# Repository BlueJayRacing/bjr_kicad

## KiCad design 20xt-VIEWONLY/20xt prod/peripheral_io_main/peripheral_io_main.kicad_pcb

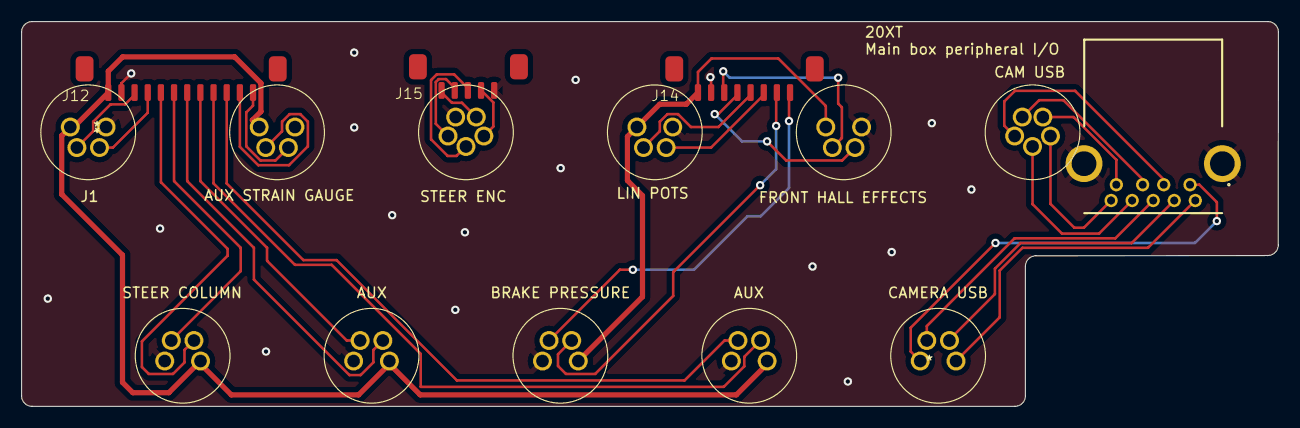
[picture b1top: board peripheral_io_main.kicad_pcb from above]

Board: 2 copper layers, 119.4 x 36.6 mm, 15 parts (0 on the bottom side), 32 nets.

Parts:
J1, J2, J3, J4, J5, J6, J7, J8, J9: Conn_01x04; CONN_T4041017041-000_TEC
J10, J11: Conn_01x05; 5pth
J12: Conn_01x12; SMD_picoblade_hori_1x12
J14: Conn_01x08; SMD_picoblade_hori_1x08
J15: Conn_01x05; SMD_picoblade_hori_1x05
J19: Conn_01x11; 1932258-1

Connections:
GND: J1.3, J2.3, J3.3, J4.3, J5.3, J6.3, J7.3, J9.3, J10.4, J12.11, J14.7, J15.1, J19.10, J19.11
unnamed: J1.2, J12.10
unnamed: J1.4, J12.9
unnamed: J10.1, J15.2
unnamed: J10.2, J15.5
unnamed: J10.3, J15.4
unnamed: J10.5, J15.3
unnamed: J11.1, J19.5
unnamed: J11.2, J19.4
unnamed: J11.3, J19.2
unnamed: J11.4, J19.3
unnamed: J11.5, J19.6
unnamed: J5.4, J12.1
unnamed: J5.2, J12.2
unnamed: J4.4, J12.3
unnamed: J4.2, J12.4
unnamed: J3.4, J12.5
unnamed: J3.2, J12.6
unnamed: J2.4, J12.7
unnamed: J2.2, J12.8
unnamed: J7.4, J14.1
unnamed: J7.2, J14.2
unnamed: J9.4, J14.3
unnamed: J9.2, J14.4
unnamed: J6.4, J14.5
unnamed: J6.2, J14.6
unnamed: J8.3, J19.1
unnamed: J8.4, J19.7
unnamed: J8.2, J19.8
unnamed: J8.1, J19.9
oth5v: J6.1, J7.1, J9.1, J14.8
sg5v: J1.1, J2.1, J3.1, J4.1, J5.1, J12.12

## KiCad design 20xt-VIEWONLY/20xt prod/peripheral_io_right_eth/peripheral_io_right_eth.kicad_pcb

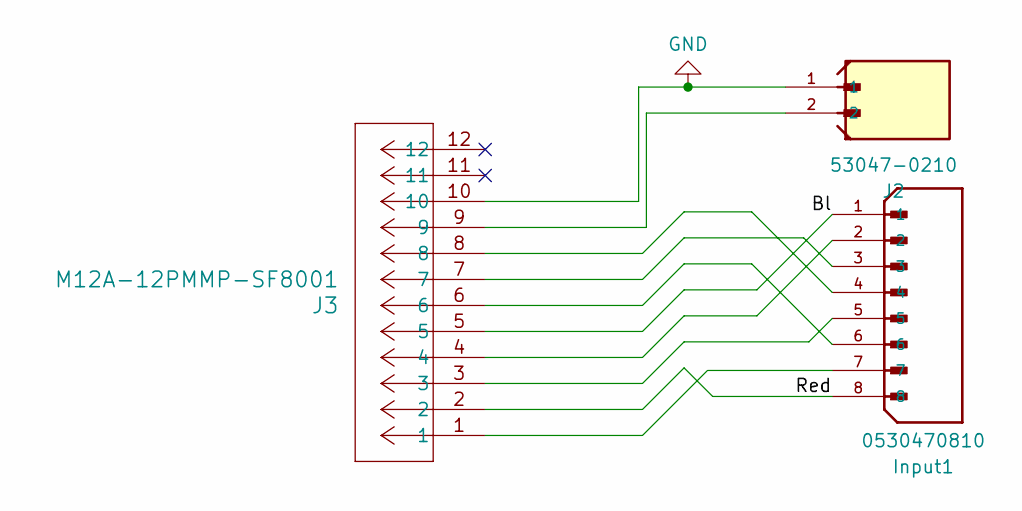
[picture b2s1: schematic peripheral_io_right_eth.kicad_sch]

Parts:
Input1: 0530470810; SMD_picoblade_hori_1x08; PARTREV B
J2: 53047-0210; SMD_picoblade_hori_1x02; PARTREV 04/19/2022
J3: M12A-12PMMP-SF8001; CONN_M12A-12PMMP-SF8001_AMP

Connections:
/Bl: Input1.1, J3.5
/Red: Input1.8, J3.2
GND: J2.1, J3.10
unnamed: Input1.2, J3.4
unnamed: Input1.3, J3.7
unnamed: Input1.4, J3.8
unnamed: Input1.5, J3.3
unnamed: Input1.6, J3.6
unnamed: Input1.7, J3.1
unnamed: J2.2, J3.9

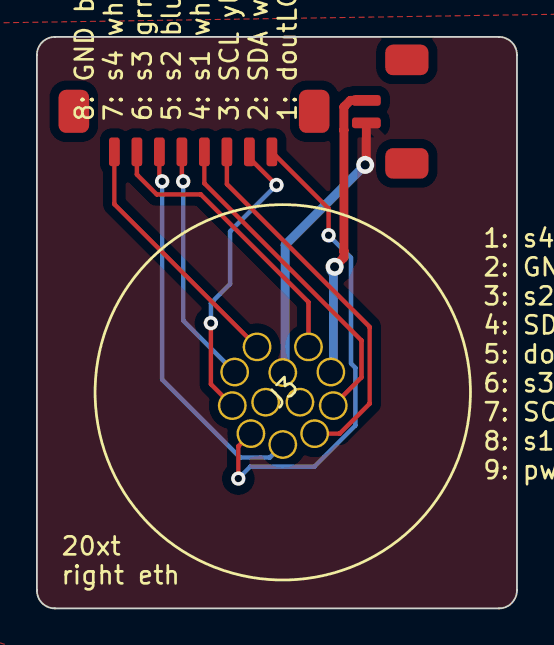
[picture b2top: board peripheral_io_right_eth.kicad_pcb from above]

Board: 2 copper layers, 26.7 x 31.8 mm, 3 parts (0 on the bottom side), 10 nets.

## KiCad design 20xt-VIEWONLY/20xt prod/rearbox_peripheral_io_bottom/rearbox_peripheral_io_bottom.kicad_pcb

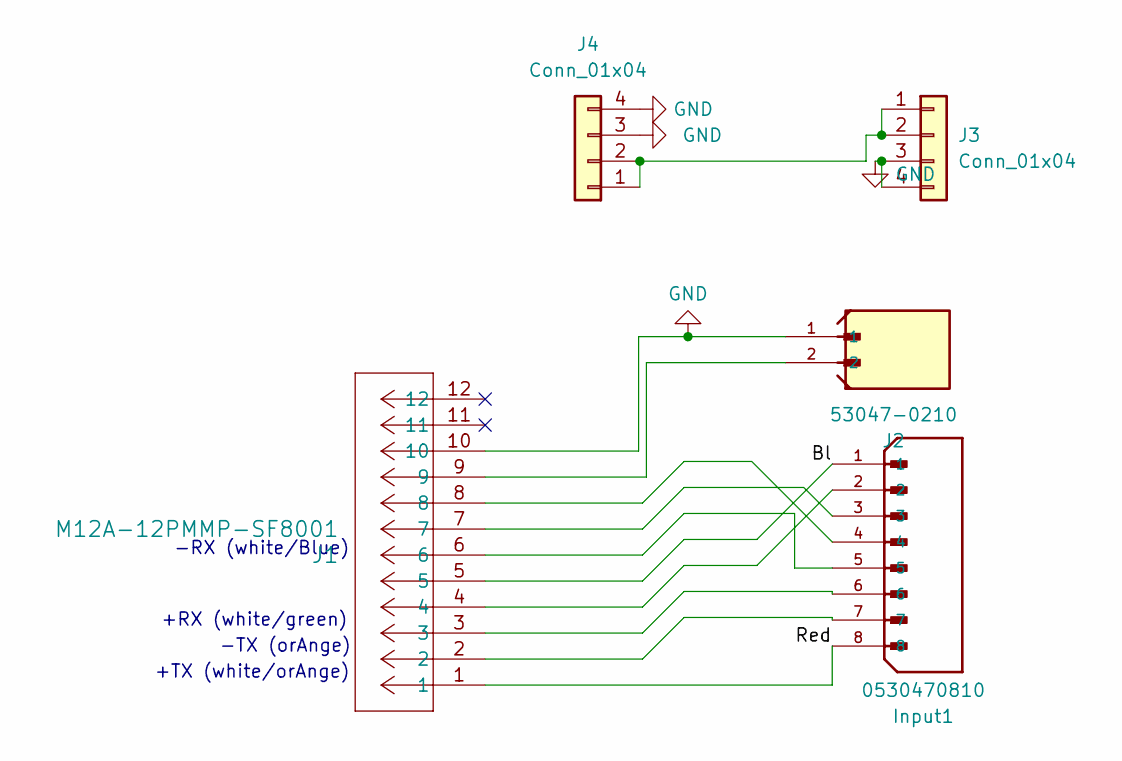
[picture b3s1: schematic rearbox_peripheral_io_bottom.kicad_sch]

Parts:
Input1: 0530470810; SMD_picoblade_hori_1x08; PARTREV B
J1: M12A-12PMMP-SF8001; CONN_M12A-12PMMP-SF8001_AMP
J2: 53047-0210; SMD_picoblade_hori_1x02; PARTREV 04/19/2022
J3: Conn_01x04; CONN_T4041017041-000_TEC
J4: Conn_01x04; SMD_picoblade_hori_1x04

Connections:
/Bl: Input1.1, J1.5
/Red: Input1.8, J1.1
GND: J1.10, J2.1, J3.3, J3.4, J4.3, J4.4
unnamed: Input1.2, J1.4
unnamed: Input1.3, J1.7
unnamed: Input1.4, J1.8
unnamed: Input1.5, J1.6
unnamed: Input1.6, J1.3
unnamed: Input1.7, J1.2
unnamed: J1.9, J2.2
unnamed: J3.1, J3.2, J4.1, J4.2

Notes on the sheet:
-RX (white/Blue)
-TX (orAnge)
+RX (white/green)
+TX (white/orAnge)

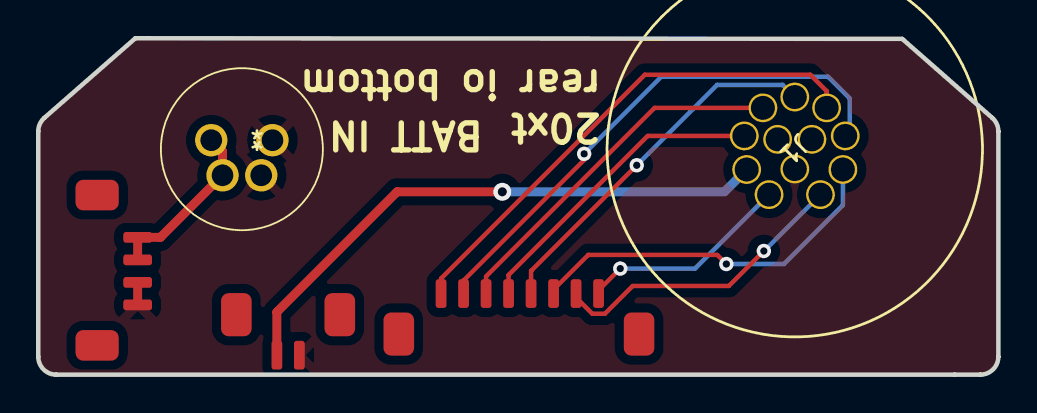
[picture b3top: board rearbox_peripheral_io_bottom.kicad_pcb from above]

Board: 2 copper layers, 53.3 x 18.7 mm, 5 parts (0 on the bottom side), 11 nets.

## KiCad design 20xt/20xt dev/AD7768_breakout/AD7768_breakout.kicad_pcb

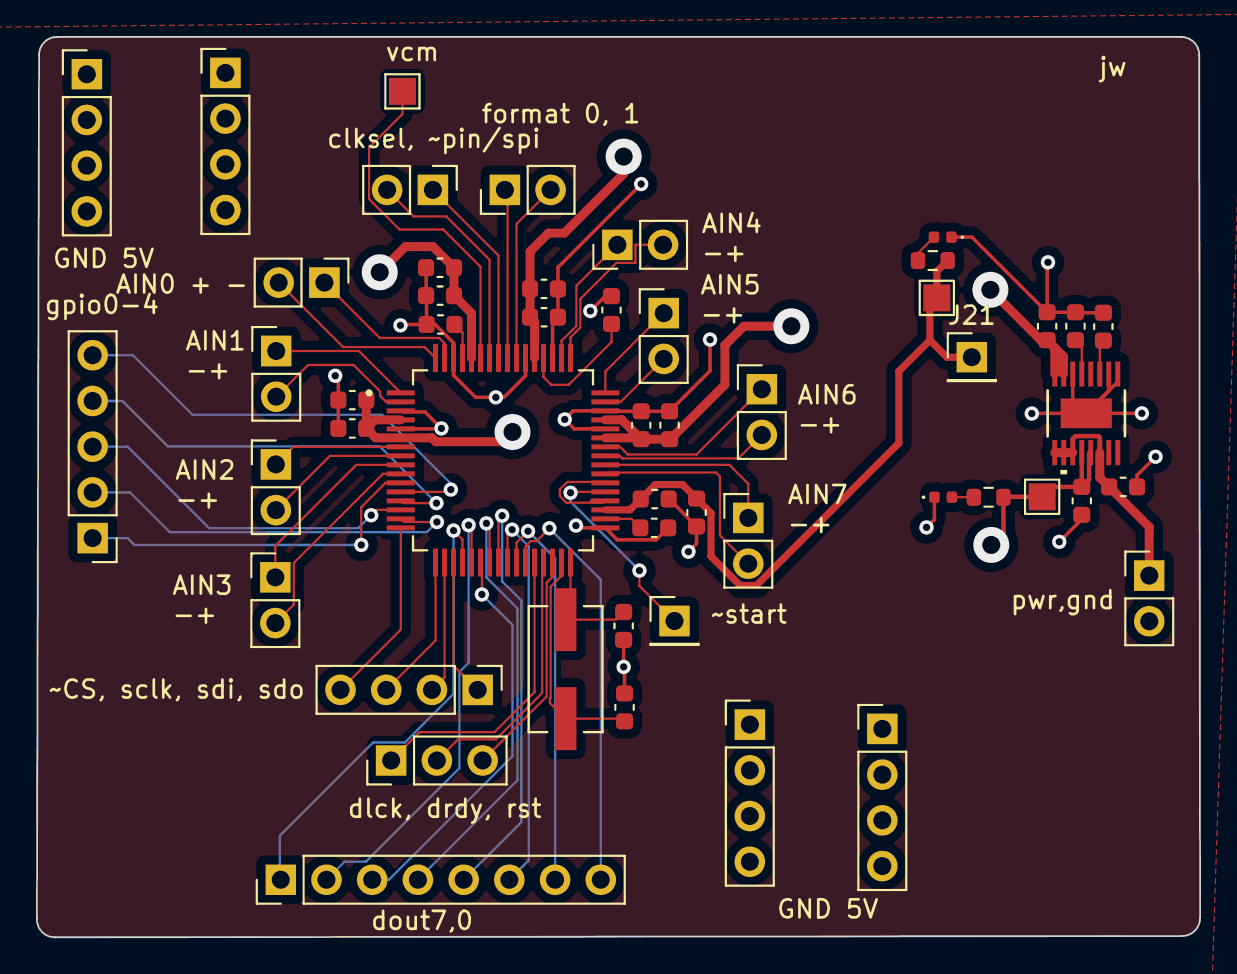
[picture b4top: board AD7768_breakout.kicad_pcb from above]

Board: 4 copper layers, 64.6 x 50.0 mm, 51 parts (0 on the bottom side), 56 nets.

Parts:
C1, C2, C3, C5, C18, C20: 1uF; C_0603_1608Metric
C4, C6, C7, C13, C15, C17, C19: 0.1uF; C_0603_1608Metric
C8, C9: 35pF; C_0603_1608Metric
C12, C14, C16, C21, C22: 100uF; C_0603_1608Metric
D1, D2: LED; D_0402_1005Metric
J1, J2, J3, J4, J5, J6, J7, J8, J9, J14, J17: Conn_01x02; PinHeader_1x02_P2.54mm_Vertical
J10, J21: Conn_01x01; PinHeader_1x01_P2.54mm_Vertical
J11: Conn_01x05; PinHeader_1x05_P2.54mm_Vertical
J12, J15, J16, J19, J20: Conn_01x04; PinHeader_1x04_P2.54mm_Vertical
J13: Conn_01x03; PinHeader_1x03_P2.54mm_Vertical
J18: Conn_01x08; PinHeader_1x08_P2.54mm_Vertical
R2, R3: R; R_0603_1608Metric
TP1, TP2, TP3: TestPoint; TestPoint_Pad_1.5x1.5mm
U1: AD7768BSTZ; QFP50P1200X1200X160-64N
U2: LT6658AHMSE-5-PBF; MSE_16_ADI
Y1: ECS-160-20-3X-TR; XTAL_ECS-160-20-3X-TR

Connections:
3v3: C16.1, C17.1, J21.1, R3.1, TP3.1, U1.35 (IOVDD)
5v: C6.2, C7.2, C12.1, C13.1, C14.1, C15.1, C18.1, C20.1, C21.2, C22.2, J15.1, J15.2, J15.3, J15.4, J19.1, J19.2, J19.3, J19.4, R2.1, TP2.1, U1.4 (AVDD1A), U1.6 (REF1+), U1.43 (REF2+), U1.45 (AVDD1B), U1.53 (AVDD2B), U1.60 (AVDD2A), U2.7 (VOUT2_S), U2.8 (VOUT2_F), U2.12 (VOUT1_F), U2.13 (VOUT1_S)
GND: C1.2, C2.2, C3.2, C4.2, C5.2, C6.1, C7.1, C8.1, C9.1, C12.2, C13.2, C14.2, C15.2, C16.2, C17.2, C18.2, C19.2, C20.2, C21.1, C22.1, D1.1 (K), D2.1 (K), J9.2, J16.1, J16.2, J16.3, J16.4, J20.1, J20.2, J20.3, J20.4, U1.3 (AVSS1A), U1.5 (REF1-), U1.33 (DGND), U1.44 (REF2-), U1.46 (AVSS1B), U1.51 (AVSS2B), U1.54 (AVSS), U1.62 (AVSS2A), U2.1 (GND), U2.2 (GND), U2.6 (GND), U2.EPAD
unnamed: D1.2 (A), R2.2
unnamed: D2.2 (A), R3.2
unnamed: J1.1, U1.63 (AIN0-)
unnamed: J1.2, U1.64 (AIN0+)
unnamed: J2.1, U1.1 (AIN1-)
unnamed: J2.2, U1.2 (AIN1+)
unnamed: J3.1, U1.7 (AIN2-)
unnamed: J3.2, U1.8 (AIN2+)
unnamed: J4.1, U1.9 (AIN3-)
unnamed: J4.2, U1.10 (AIN3+)
unnamed: J5.1, U1.50 (AIN4-)
unnamed: J5.2, U1.49 (AIN4+)
unnamed: J6.1, U1.48 (AIN5-)
unnamed: J6.2, U1.47 (AIN5+)
unnamed: J7.1, U1.42 (AIN6-)
unnamed: J7.2, U1.41 (AIN6+)
unnamed: J8.1, U1.40 (AIN7-)
unnamed: J8.2, U1.39 (AIN7+)
unnamed: J10.1, U1.37 (~START)
unnamed: J11.1, U1.11 (FILTER/GPIO4)
unnamed: J11.2, U1.15 (MODE3/GPIO3)
unnamed: J11.3, U1.14 (MODE2/GPIO2)
unnamed: J11.4, U1.13 (MODE1/GPIO1)
unnamed: J11.5, U1.12 (MODE0/GPIO0)
unnamed: J12.1, U1.19 (DEC0/SDO)
unnamed: J12.2, U1.18 (DEC1/SDI)
unnamed: J12.3, U1.17 (ST1/SCLK)
unnamed: J12.4, U1.16 (ST0/~CS)
unnamed: J13.1, U1.28 (DCLK)
unnamed: J13.2, U1.29 (~DRDY)
unnamed: J14.1, U1.57 (~PIN/SPI)
unnamed: J14.2, U1.58 (CLK_SEL)
unnamed: J17.1, U1.56 (FORMAT0)
unnamed: J17.2, U1.55 (FORMAT1)
unnamed: J18.1, U1.20 (DOUT7)
unnamed: J18.2, U1.21 (DOUT6)
unnamed: J18.3, U1.22 (DOUT5)
unnamed: J18.4, U1.23 (DOUT4)
unnamed: J18.5, U1.24 (DOUT3)
unnamed: J18.6, U1.25 (DOUT2)
unnamed: J18.7, U1.26 (DOUT1)
unnamed: J18.8, U1.27 (DOUT0)
unnamed: C1.1, U1.34 (DREGCAP)
unnamed: C5.1, U1.61 (REGCAPA)
unnamed: C2.1, U1.52 (REGCAPB)
unnamed: TP1.1, U1.59 (VCM)
unnamed: C8.2, U1.31 (XTAL1), Y1.2
unnamed: C9.2, U1.32 (XTAL2/MCLK), Y1.1
unnamed: U1.36 (~SYNC_IN), U1.38 (~SYNC_OUT)
unnamed: C3.1, U2.3 (BYPASS)
unnamed: C4.1, U2.5 (NR)
rst: J13.3, U1.30 (~RESET)
vin: C19.1, J9.1, U2.9 (*OD), U2.10 (VIN2), U2.11 (VIN1), U2.14 (VIN)

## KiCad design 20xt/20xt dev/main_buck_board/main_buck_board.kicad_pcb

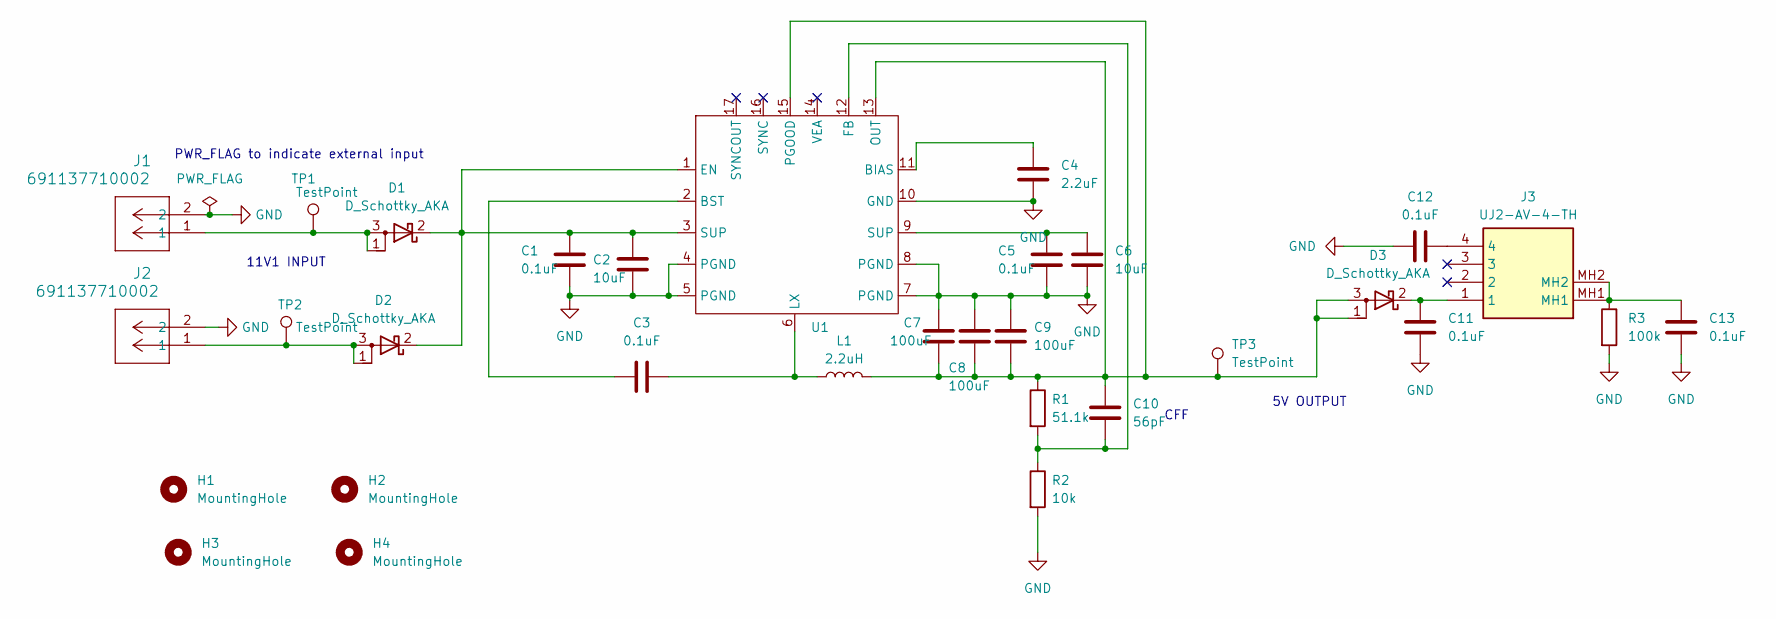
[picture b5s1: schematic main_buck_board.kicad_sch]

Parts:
C1, C3, C5, C11, C12, C13: 0.1uF; C_0402_1005Metric
C2, C6: 10uF; C_0603_1608Metric
C4: 2.2uF; C_0402_1005Metric
C7, C8, C9: 100uF; C_1206_3216Metric
C10: 56pF; C_0201_0603Metric
D1, D2, D3: D_Schottky_AKA; DPAK228P990X239-4N
H1, H2, H3, H4: MountingHole; MountingHole_2.2mm_M2
J1, J2: 691137710002; CONN2_710002_WRE
J3: UJ2-AV-4-TH; UJ2AV4TH; Mouser Part Number 490-UJ2-AV-4-TH
L1: 2.2uH; C_0402_1005Metric
R1: 51.1k; R_0603_1608Metric
R2: 10k; R_0603_1608Metric
R3: 100k; R_0603_1608Metric
TP1, TP2, TP3: TestPoint; TestPoint_Pad_D1.0mm
U1: 21-100700_90-100240_ADI

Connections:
GND: C1.2, C2.2, C4.2, C5.2, C6.2, C7.1, C8.1, C9.1, C11.2, C12.1, C13.2, J1.2, J2.2, R2.2, R3.2, U1.4 (PGND), U1.5 (PGND), U1.7 (PGND), U1.8 (PGND), U1.10 (GND)
unnamed: C5.1, C6.1, U1.9 (SUP)
unnamed: C12.2, J3.4
unnamed: C13.1, J3.MH1, J3.MH2, R3.1
unnamed: D1.1 (A), D1.3 (A), J1.1, TP1.1
unnamed: C1.1, C2.1, D1.2 (K), D2.2 (K), U1.1 (EN), U1.3 (SUP)
unnamed: D2.1 (A), D2.3 (A), J2.1, TP2.1
unnamed: C11.1, D3.2 (K), J3.1
unnamed: C4.1, U1.11 (BIAS)
unnamed: C3.1, U1.2 (BST)
unnamed: C10.2, R1.2, R2.1, U1.12 (FB)
unnamed: C3.2, L1.1, U1.6 (LX)
unnamed: C7.2, C8.2, C9.2, C10.1, D3.1 (A), D3.3 (A), L1.2, R1.1, TP3.1, U1.13 (OUT), U1.15 (PGOOD)

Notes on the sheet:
5V OUTPUT
CFF
PWR_FLAG to indicate external input
11V1 INPUT

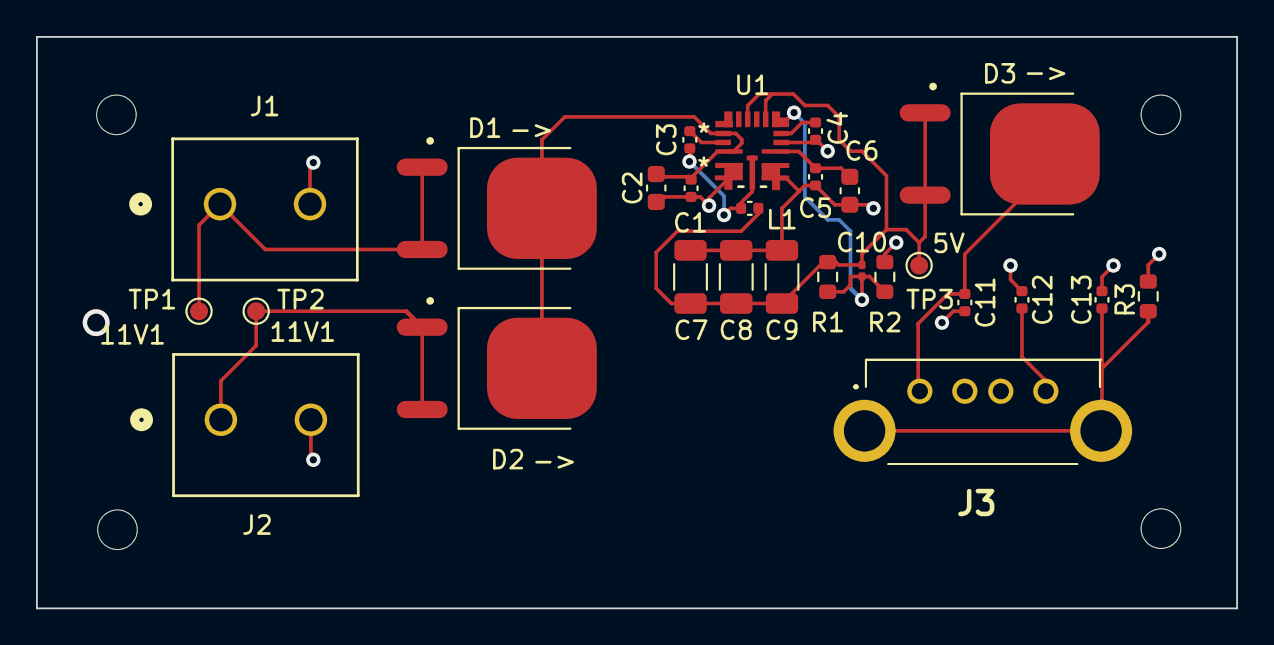
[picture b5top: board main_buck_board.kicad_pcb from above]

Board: 4 copper layers, 66.7 x 31.8 mm, 31 parts (0 on the bottom side), 13 nets.

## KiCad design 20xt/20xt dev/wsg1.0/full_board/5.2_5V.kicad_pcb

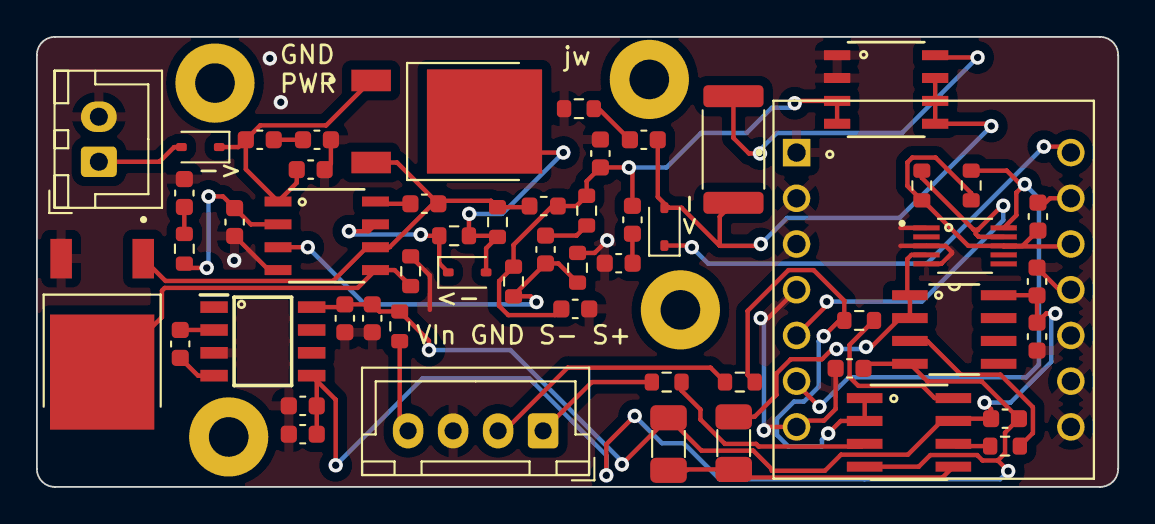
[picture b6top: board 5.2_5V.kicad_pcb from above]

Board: 2 copper layers, 60.1 x 25.0 mm, 59 parts (0 on the bottom side), 36 nets.

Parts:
C1, C3, C10: 0.1u; C_0603_1608Metric
C2: 10u; C_0603_1608Metric
C4, C12: 470u; C_0603_1608Metric
C5, C6: 15u; C_0603_1608Metric
C8: 33p; C_0603_1608Metric
C9: 7.5n; C_0603_1608Metric
C11: 2.2n; C_0603_1608Metric
C13, C14: 22u; C_0603_1608Metric
C15, C16, C17, C19, C20, C23: 10uF; C_0603_1608Metric
C18, C21, C22: 100nF; C_0603_1608Metric
D4, D5, D6: D_Schottky; D_SOD-323
H1, H2, H3, H4: MountingHole; MountingHole_2.2mm_M2_Pad
J1: Conn_01x04_Socket; JST_XH_B4B-XH-A_1x04_P2.50mm_Vertical
J2: B2B-XH-A_LF__SN_; JST_XH_B2B-XH-A_1x02_P2.50mm_Vertical
L1: L; L_0603_1608Metric
Q1, Q2: NMOS; TRANS_BTS3060TFATMA1
R1: 250k; R_2512_6332Metric
R2: 1; R_0603_1608Metric
R3, R4, R9: 4.7k; R_0603_1608Metric
R5: 4.75K; R_0603_1608Metric
R6: 22.1K; R_0603_1608Metric
R7: 5; R_0603_1608Metric
R8: 1k; R_0603_1608Metric
R10: 1.2k; R_0603_1608Metric
R11: 2.7k; R_0603_1608Metric
R12: 10; R_0603_1608Metric
R13, R14, R18: 1K; R_0603_1608Metric
R15, R16: R; R_1206_3216Metric
R17: 200; R_0603_1608Metric
U1: TPS7150QD; D8_TEX
U2: MOUDLE-SEEEDUINO-XIAO-ESP32C3; MODULE_102010388
U3: ADS1115IDGST; ADS115IDGST_SOP50P490X110-10N
U4: NCP3020ADR2G; SOIC8_ONS_NCP3020ADR
U8: LMC7660; SOIC127P600X175-8N
U9: AD620; R_8_ADI_AD620ARZ
U12: LM358DR

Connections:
3V3: C3.1, R3.1, R4.1, U2.12 (3V3), U3.8 (VDD)
5V: C2.1, D4.2 (A), R1.2, U1.5 (OUT), U1.6 (OUT), U1.7 (SENSE/FB)
5V2: C1.1, C12.1, C13.1, L1.2, R9.1, R10.1, U1.3 (IN), U1.4 (IN)
GND: C1.2, C3.2, C4.2, C6.2, C8.2, C9.2, C12.2, C14.2, C15.2, C16.2, C18.2, C19.2, C20.2, C21.2, C23.2, J1.3, J2.2, Q2.3 (S), R2.2, R6.2, R11.2, U1.1 (GND), U1.2 (*EN), U2.1 (PA02_A0_D0), U2.2 (PA4_A1_D1), U2.3 (PA10_A2_D2), U2.4 (PA11_A3_D3), U2.7 (PB08_A6_D6_TX), U2.8 (PB09_A7_D7_RX), U2.9 (PA7_A8_D8_SCK), U2.10 (PA5_A9_D9_MISO), U2.11 (PA6_A10_D10_MOSI), U2.13 (GND), U3.1 (ADDR), U3.3 (GND), U3.5 (AIN1), U4.4 (GND), U8.3 (GND)
unnamed: C2.2, R2.1
unnamed: C5.2, C6.1
unnamed: C9.1, R5.2
unnamed: C11.1, R10.2
unnamed: C13.2, C14.1
unnamed: D4.1 (K), U2.14 (5V)
unnamed: D5.2 (A), J2.1
unnamed: C4.1, C5.1, D5.1 (K), Q1.1 (D), U4.1 (VCC)
unnamed: D6.2 (A), Q1.2 (G), R7.2, R8.1
unnamed: D6.1 (K), R7.1, U4.7 (HSDR)
unnamed: J1.1, R14.1
unnamed: J1.2, R13.1
unnamed: J1.4, R12.1
unnamed: C10.2, L1.1, Q1.3 (S), Q2.1 (D), R8.2, U4.6 (VSW)
unnamed: Q2.2 (G), R6.1, U4.5 (LSDR)
unnamed: R17.2, U9.8 (Rg)
unnamed: R18.1, U9.6
unnamed: R1.1, U1.8 (PG)
unnamed: R3.2, U2.5 (PA8_A4_D4_SDA), U3.9 (SDA)
unnamed: R4.2, U2.6 (PA9_A5_D5_SCL), U3.10 (SCL)
unnamed: C10.1, U4.8 (BST)
unnamed: C8.1, R5.1, U4.2 (COMP)
unnamed: C11.2, R9.2, R11.1, U4.3 (FB)
unnamed: C17.1, U8.2 (CAP+)
unnamed: C17.2, U8.4 (CAP-)
unnamed: R14.2, U9.3 (+)
unnamed: R13.2, R17.1, U9.1 (Rg), U9.2 (-)
unnamed: R15.2, R16.1, U9.5 (Ref)
unnamed: R18.2, U12.3 (1IN+)
unnamed: C18.1, C19.1, C22.2, C23.1, U8.5 (VOUT), U9.4 (Vs-), U12.4 (GND)
unnamed: C15.1, C16.1, C20.1, C21.1, C22.1, R12.2, R15.1, U8.8 (V+), U9.7 (Vs+), U12.8 (VCC)
ampSig: R16.2, U3.4 (AIN0), U12.1 (1OUT), U12.2 (1IN-)

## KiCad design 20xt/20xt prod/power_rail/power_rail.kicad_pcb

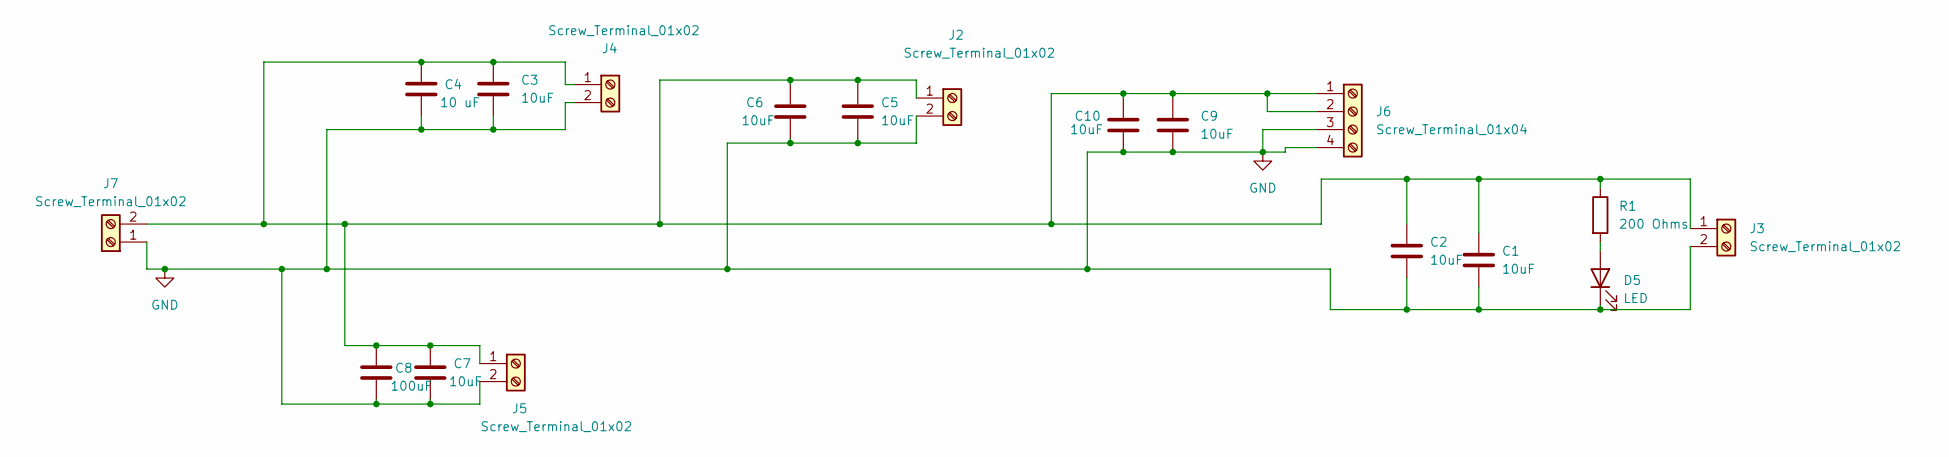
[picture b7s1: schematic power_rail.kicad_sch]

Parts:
C1, C2, C3, C5, C6, C7, C9, C10: 10uF; C_0603_1608Metric_Pad1.08x0.95mm_HandSolder
C4: 10 uF; C_0603_1608Metric_Pad1.08x0.95mm_HandSolder
C8: 100uF; C_0603_1608Metric_Pad1.08x0.95mm_HandSolder
D5: LED; LED_0603_1608Metric_Pad1.05x0.95mm_HandSolder
J2, J3, J4, J5, J7: Screw_Terminal_01x02; JST_XH_S2B-XH-A-1_1x02_P2.50mm_Horizontal
J6: Screw_Terminal_01x04; MOLEX_0532610471
R1: 200 Ohms; R_0603_1608Metric_Pad0.98x0.95mm_HandSolder

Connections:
GND: C1.2, C2.2, C3.2, C4.2, C5.2, C6.2, C7.2, C8.2, C9.2, C10.2, D5.1 (K), J2.2, J3.2, J4.2, J5.2, J6.3, J6.4, J7.1
unnamed: D5.2 (A), R1.2
unnamed: C1.1, C2.1, C3.1, C4.1, C5.1, C6.1, C7.1, C8.1, C9.1, C10.1, J2.1, J3.1, J4.1, J5.1, J6.1, J6.2, J7.2, R1.1

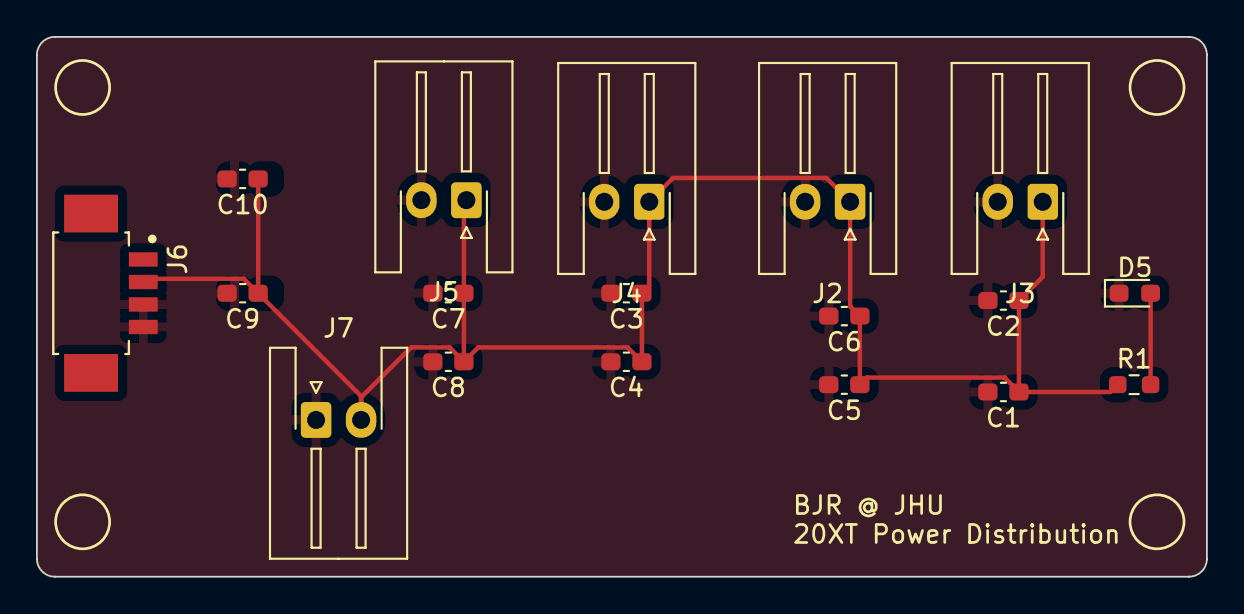
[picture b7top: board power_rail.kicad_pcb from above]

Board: 2 copper layers, 65.0 x 30.0 mm, 18 parts (0 on the bottom side), 3 nets.
